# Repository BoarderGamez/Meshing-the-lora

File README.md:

# Meshing the LoRa
This is a compact LoRa puck for all your needs such as meshtastic. I made this because I'm on my way to getting my ham radio licence and I thought this would be a cool accompanying thing. (also meshtastic is peak)
## Where did this name come from?
I intend to use it for meshtastic so I thought of this name!

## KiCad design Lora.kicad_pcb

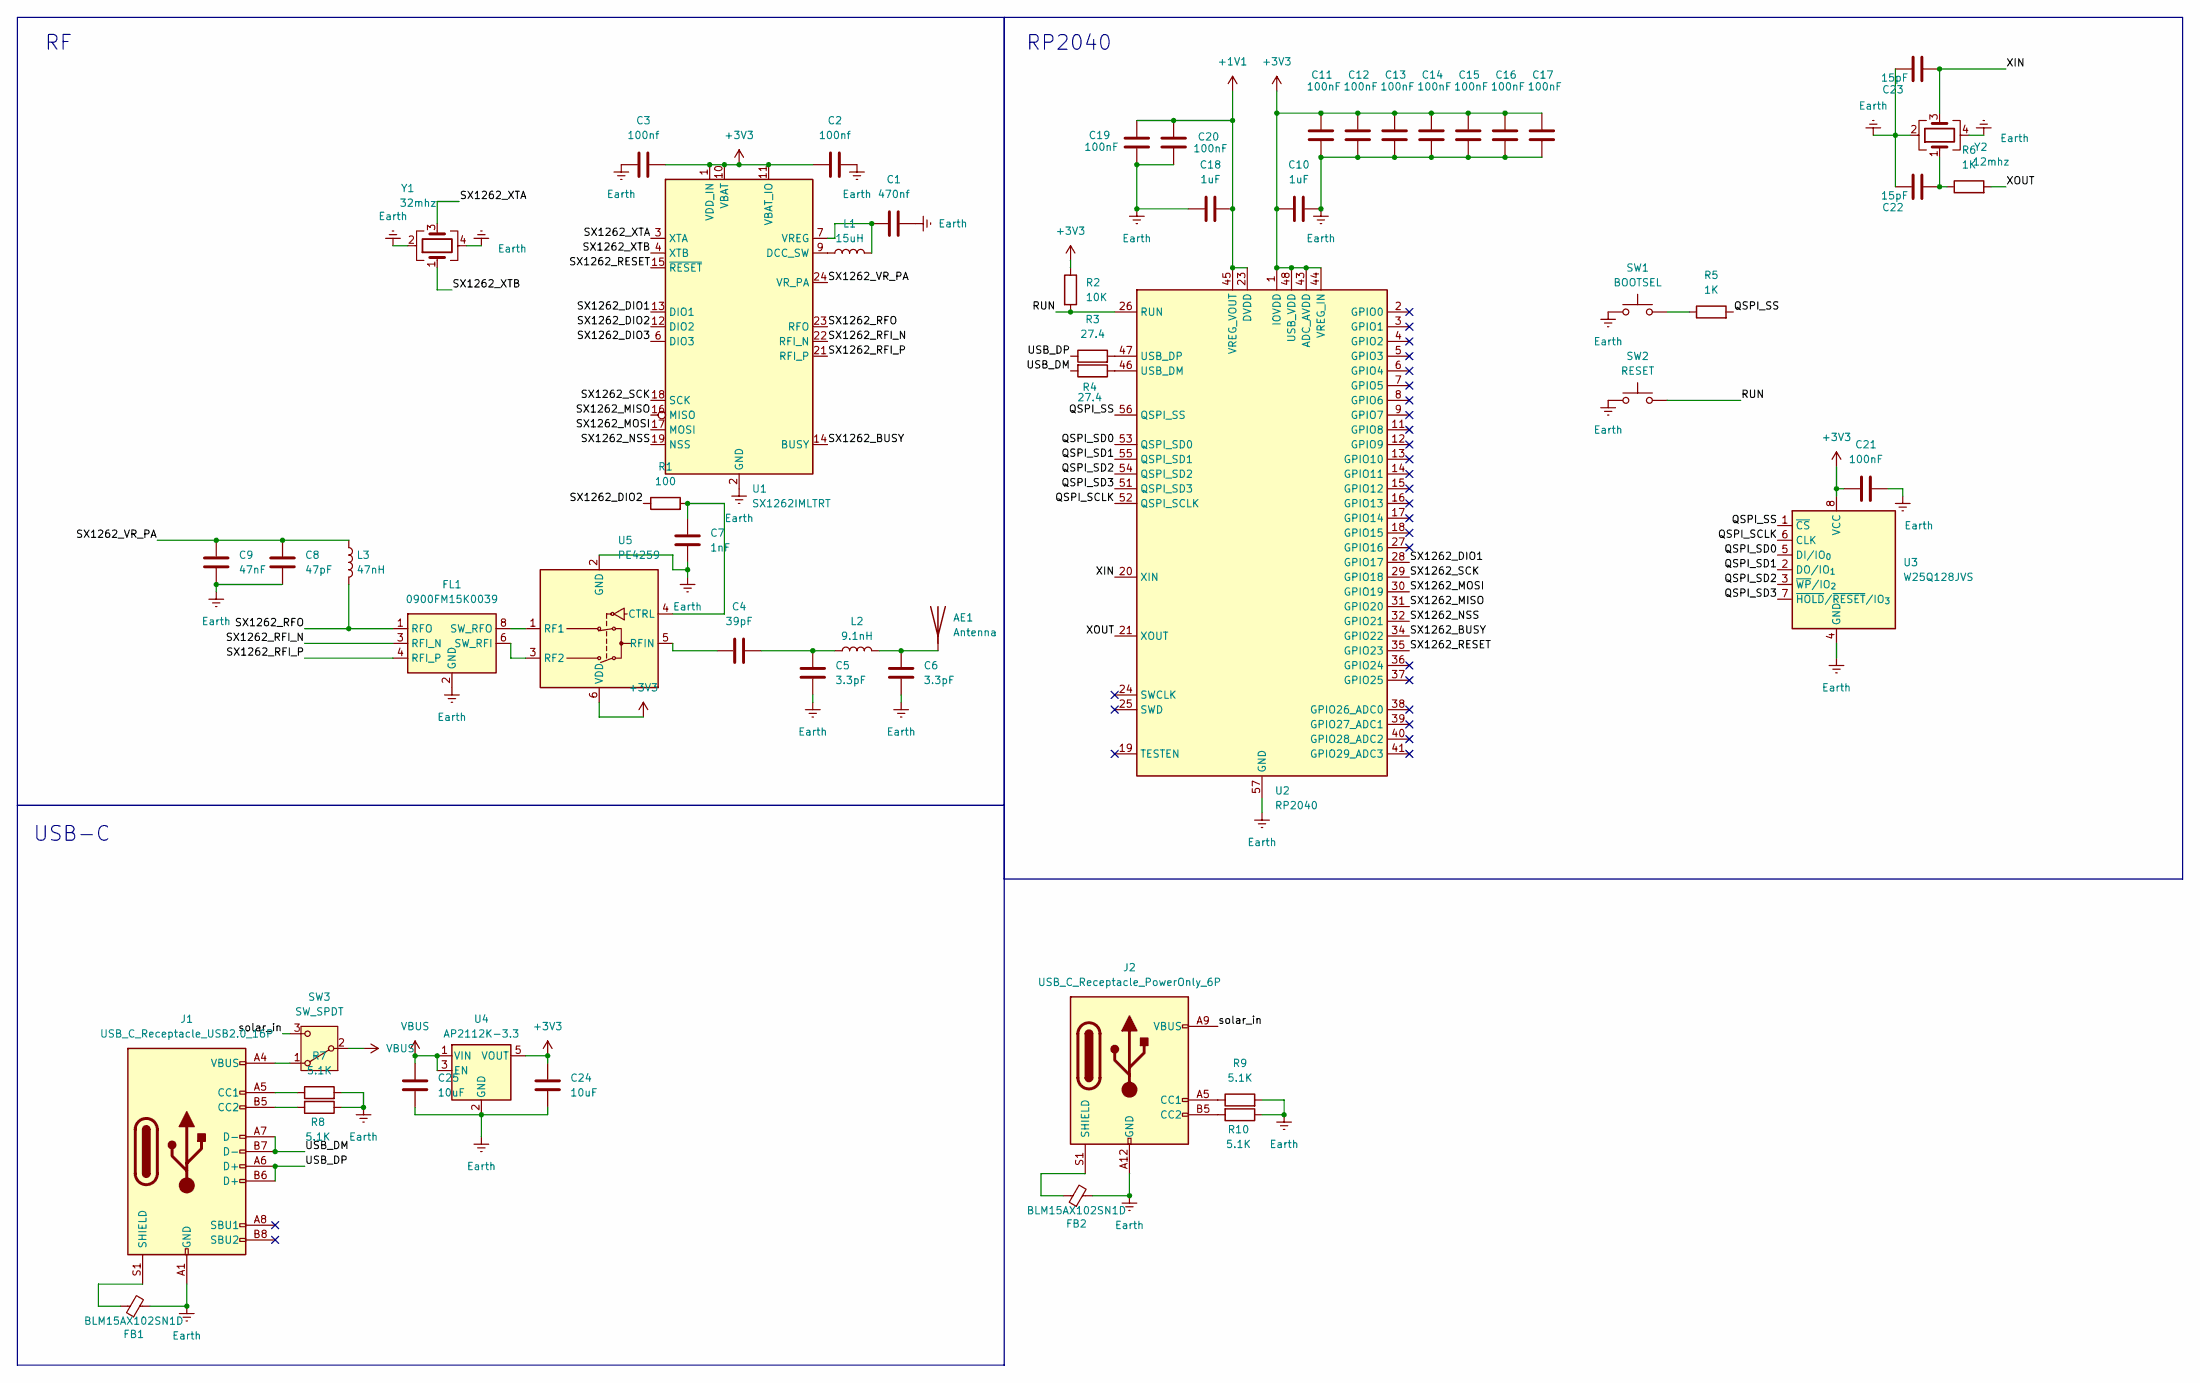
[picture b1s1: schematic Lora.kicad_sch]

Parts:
AE1: Antenna; PinSocket_1x01_P2.54mm_Vertical
C1: 470nf; C_0402_1005Metric
C2, C3: 100nf; C_0402_1005Metric
C4: 39pF; C_0402_1005Metric
C5, C6: 3.3pF; C_0402_1005Metric
C7: 1nF; C_0402_1005Metric
C8: 47pF; C_0402_1005Metric
C9: 47nF; C_0402_1005Metric
C10, C18: 1uF; C_0402_1005Metric
C11, C12, C13, C14, C15, C16, C17, C19, C20, C21: 100nF; C_0402_1005Metric
C22, C23: 15pF; C_0402_1005Metric
C24, C25: 10uF; C_0402_1005Metric
FB1, FB2: BLM15AX102SN1D; L_0402_1005Metric
FL1: 0900FM15K0039; Balun_Johanson_0900FM15K0039
J1: USB_C_Receptacle_USB2.0_16P; USB_C_Receptacle_GCT_USB4105-xx-A_16P_TopMnt_Horizontal
J2: USB_C_Receptacle_PowerOnly_6P; USB_C_Receptacle_GCT_USB4125-xx-x_6P_TopMnt_Horizontal
L1: 15uH; L_0402_1005Metric
L2: 9.1nH; L_0402_1005Metric
L3: 47nH; L_0402_1005Metric
R1: 100; R_0402_1005Metric
R2: 10K; R_0402_1005Metric
R3, R4: 27.4; R_0402_1005Metric
R5, R6: 1K; R_0402_1005Metric
R7, R8, R9, R10: 5.1K; R_0402_1005Metric
SW1: BOOTSEL; SW_Tactile_SPST_NO_Straight_CK_PTS636Sx25SMTRLFS
SW2: RESET; SW_Tactile_SPST_NO_Straight_CK_PTS636Sx25SMTRLFS
SW3: SW_SPDT; SW_SPDT_CK_JS102011SAQN
U1: SX1262IMLTRT; QFN-24-1EP_4x4mm_P0.5mm_EP2.6x2.6mm
U2: RP2040; QFN-56-1EP_7x7mm_P0.4mm_EP3.2x3.2mm
U3: W25Q128JVS; SOIC-8_5.3x5.3mm_P1.27mm
U4: AP2112K-3.3; SOT-23-5
U5: PE4259; SOT-363_SC-70-6
Y1: 32mhz; Crystal_SMD_3225-4Pin_3.2x2.5mm
Y2: 12mhz; Crystal_SMD_Abracon_ABM8G-4Pin_3.2x2.5mm

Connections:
+1V1: C18.2, C19.1, C20.1, U2.23 (DVDD), U2.45 (VREG_VOUT), U2.50 (DVDD)
+3V3: C2.1, C3.2, C10.1, C11.1, C12.1, C13.1, C14.1, C15.1, C16.1, C17.1, C21.1, C24.1, R2.1, U1.1 (VDD_IN), U1.10 (VBAT), U1.11 (VBAT_IO), U2.1 (IOVDD), U2.10 (IOVDD), U2.22 (IOVDD), U2.33 (IOVDD), U2.42 (IOVDD), U2.43 (ADC_AVDD), U2.44 (VREG_IN), U2.48 (USB_VDD), U2.49 (IOVDD), U3.8 (VCC), U4.5 (VOUT), U5.6 (VDD)
/QSPI_SCLK: U2.52 (QSPI_SCLK), U3.6 (CLK)
/QSPI_SD0: U2.53 (QSPI_SD0), U3.5 (DI/IO_{0})
/QSPI_SD1: U2.55 (QSPI_SD1), U3.2 (DO/IO_{1})
/QSPI_SD2: U2.54 (QSPI_SD2), U3.3 (~WP/IO_{2})
/QSPI_SD3: U2.51 (QSPI_SD3), U3.7 (~HOLD/~RESET/IO_{3})
/QSPI_SS: R5.2, U2.56 (QSPI_SS), U3.1 (~CS)
/RUN: R2.2, SW2.2, U2.26 (RUN)
/SX1262_BUSY: U1.14 (BUSY), U2.34 (GPIO22)
/SX1262_DIO1: U1.13 (DIO1), U2.28 (GPIO17)
/SX1262_DIO2: R1.1, U1.12 (DIO2)
/SX1262_DIO3: U1.6 (DIO3)
/SX1262_MISO: U1.16 (MISO), U2.31 (GPIO20)
/SX1262_MOSI: U1.17 (MOSI), U2.30 (GPIO19)
/SX1262_NSS: U1.19 (NSS), U2.32 (GPIO21)
/SX1262_RESET: U1.15 (~RESET), U2.35 (GPIO23)
/SX1262_RFI_N: FL1.3 (RFI_N), U1.22 (RFI_N)
/SX1262_RFI_P: FL1.4 (RFI_P), U1.21 (RFI_P)
/SX1262_RFO: FL1.1 (RFO), L3.2, U1.23 (RFO)
/SX1262_SCK: U1.18 (SCK), U2.29 (GPIO18)
/SX1262_VR_PA: C8.1, C9.1, L3.1, U1.24 (VR_PA)
/SX1262_XTA: U1.3 (XTA), Y1.3
/SX1262_XTB: U1.4 (XTB), Y1.1
/USB_DM: J1.A7 (D-), J1.B7 (D-), R4.2
/USB_DP: J1.A6 (D+), J1.B6 (D+), R3.1
/XIN: C23.2, U2.20 (XIN), Y2.3
/XOUT: R6.2, U2.21 (XOUT)
/solar_in: J2.A9 (VBUS), J2.B9 (VBUS), SW3.3 (C)
Earth: C1.1, C2.2, C3.1, C5.1, C6.2, C7.2, C8.2, C9.2, C10.2, C11.2, C12.2, C13.2, C14.2, C15.2, C16.2, C17.2, C18.1, C19.2, C20.2, C21.2, C22.1, C23.1, C24.2, C25.2, FB1.2, FB2.2, FL1.2 (GND), FL1.5 (GND), FL1.7 (GND), FL1.9 (GND), FL1.10 (GND), J1.A1 (GND), J1.A12 (GND), J1.B1 (GND), J1.B12 (GND), J2.A12 (GND), J2.B12 (GND), R7.2, R8.1, R9.2, R10.1, SW1.1, SW2.1, U1.2 (GND), U1.5 (GND), U1.8 (GND), U1.20 (GND), U1.25 (GND), U2.57 (GND), U3.4 (GND), U4.2 (GND), U5.2 (GND), Y1.2, Y1.4, Y2.2, Y2.4
unnamed: AE1.1 (A), C6.1, L2.2
unnamed: C4.2, C5.2, L2.1
unnamed: C22.2, R6.1, Y2.1
unnamed: FL1.6 (SW_RFI), U5.3 (RF2)
unnamed: FL1.8 (SW_RFO), U5.1 (RF1)
unnamed: J1.A5 (CC1), R7.1
unnamed: J1.B5 (CC2), R8.2
unnamed: FB1.1, J1.S1 (SHIELD)
unnamed: J2.A5 (CC1), R9.1
unnamed: J2.B5 (CC2), R10.2
unnamed: FB2.1, J2.S1 (SHIELD)
unnamed: R5.1, SW1.2
unnamed: J1.A4 (VBUS), J1.A9 (VBUS), J1.B4 (VBUS), J1.B9 (VBUS), SW3.1 (A)
unnamed: L1.1, U1.9 (DCC_SW)
unnamed: C1.2, L1.2, U1.7 (VREG)
unnamed: R4.1, U2.46 (USB_DM)
unnamed: R3.2, U2.47 (USB_DP)
unnamed: C7.1, R1.2, U5.4 (CTRL)
unnamed: C4.1, U5.5 (RFIN)
VBUS: C25.1, SW3.2 (B), U4.1 (VIN), U4.3 (EN)

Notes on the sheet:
USB-C
RP2040

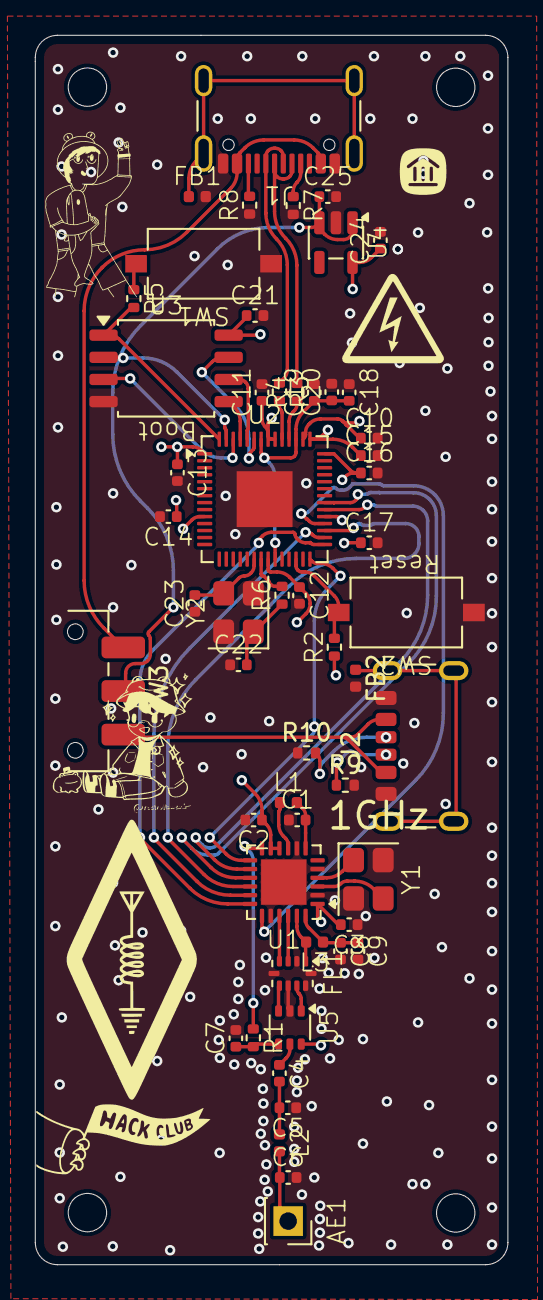
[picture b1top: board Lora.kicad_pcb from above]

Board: 4 copper layers, 27.1 x 70.5 mm, 54 parts (0 on the bottom side), 49 nets.

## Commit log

2025-11-26 added
2025-11-26 Add initial content to README.md
2025-11-28 dun x2
2025-11-28 Upload
2025-11-28 acc dun
2025-11-28 Update README with project details and images
    Added introductory information about the LoRa puck and its purpose.
2025-11-28 Add cost details for LCSC and JLCPCB
2025-11-29 Add additional image to README
2025-12-04 Rename Lora.wrl to kicad/Lora.wrl
2025-12-04 Rename Lora.kicad_sch to kicad/Lora.kicad_sch
2025-12-04 Rename Lora.kicad_prl to kicad/Lora.kicad_prl
2025-12-04 Rename Lora.kicad_pcb to kicad/Lora.kicad_pcb
2025-12-04 Rename Lora.kicad_pro to kicad/Lora.kicad_pro
